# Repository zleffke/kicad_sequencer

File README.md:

# kicad_sequencer
Transverter sequencer circuit.  Based on W6PQL Design.

### Credit where its due:
[Relay Sequencer](https://www.w6pql.com/relay_sequencer.htm) from W6PQL.

#### Versions:

w6pql_sequencer - this design is nearly identical to W6PQL's at the link above. Just a kicad implementation and variations on the layout for my own projects.

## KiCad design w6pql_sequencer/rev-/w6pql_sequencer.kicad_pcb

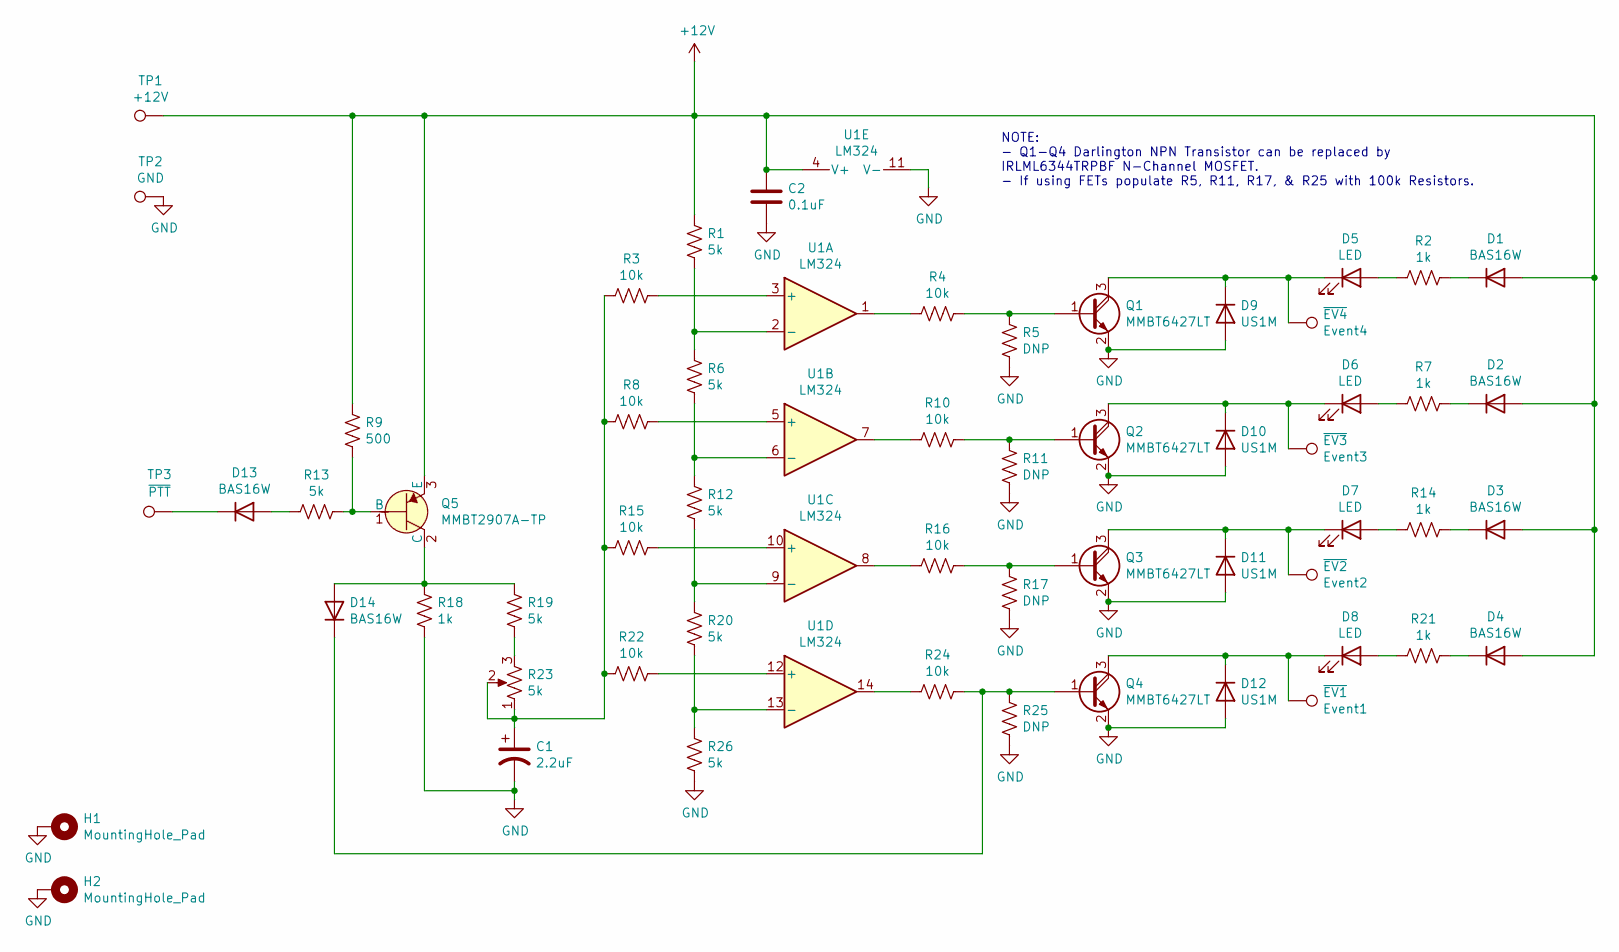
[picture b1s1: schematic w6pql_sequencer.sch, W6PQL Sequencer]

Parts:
C1: 2.2uF; CP_EIA-3216-18_Kemet-A
C2: 0.1uF; 0805
D1, D2, D3, D4, D13, D14: BAS16W; SOT-23-3
D5, D6, D7, D8: LED; LED_0805_2012Metric
D9, D10, D11, D12: US1M; D_SMA
H1, H2: MountingHole_Pad; MountingHole_3.2mm_M3_Pad_Via
Q1, Q2, Q3, Q4: MMBT6427LT; SOT-23-3
Q5: MMBT2907A-TP; SOT-23-3; MPN MMBT2907A-TP; Digi-Key_PN MMBT2907A-TPMSCT-ND
R1, R6, R12, R13, R19, R20, R26: 5k; 0805
R2, R7, R14, R18, R21: 1k; 0805
R3, R4, R8, R10, R15, R16, R22, R24: 10k; 0805
R5, R11, R17, R25: DNP; 0805
R9: 500; 0805
R23: 5k; Potentiometer_Bourns_3314G_Vertical
TP1: +12V; TestPoint_Pad_3.0x3.0mm
TP2: GND; TestPoint_Pad_3.0x3.0mm
TP3: ~PTT; TestPoint_Pad_3.0x3.0mm
U1: LM324; SOIC-14_W3.9mm
~EV1: Event1; TestPoint_Pad_4.0x4.0mm
~EV2: Event2; TestPoint_Pad_4.0x4.0mm
~EV3: Event3; TestPoint_Pad_4.0x4.0mm
~EV4: Event4; TestPoint_Pad_4.0x4.0mm

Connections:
+12V: C2.1, D1.1 (A), D2.1 (A), D3.1 (A), D4.1 (A), Q5.3 (E), R1.1, R9.1, TP1.1, U1.4 (V+)
GND: C1.2, C2.2, D9.2 (A), D10.2 (A), D11.2 (A), D12.2 (A), H1.1, H2.1, Q1.2 (E), Q2.2 (E), Q3.2 (E), Q4.2 (E), R5.1, R11.1, R17.1, R18.2, R25.1, R26.2, TP2.1, U1.11 (V-)
unnamed: C1.1, R3.2, R8.2, R15.2, R22.2, R23.1, R23.2
unnamed: D1.3 (K), R2.1
unnamed: D2.3 (K), R7.1
unnamed: D3.3 (K), R14.1
unnamed: D4.3 (K), R21.1
unnamed: D5.1 (K), D9.1 (K), Q1.3 (C), ~EV4.1
unnamed: D5.2 (A), R2.2
unnamed: D6.2 (A), R7.2
unnamed: D7.2 (A), R14.2
unnamed: D8.2 (A), R21.2
unnamed: D6.1 (K), D10.1 (K), Q2.3 (C), ~EV3.1
unnamed: D7.1 (K), D11.1 (K), Q3.3 (C), ~EV2.1
unnamed: D8.1 (K), D12.1 (K), Q4.3 (C), ~EV1.1
unnamed: D13.1 (A), R13.2
unnamed: D13.3 (K), TP3.1
unnamed: D14.1 (A), Q5.2 (C), R18.1, R19.1
unnamed: D14.3 (K), Q4.1 (B), R24.1, R25.2
unnamed: Q1.1 (B), R4.1, R5.2
unnamed: Q2.1 (B), R10.1, R11.2
unnamed: Q3.1 (B), R16.1, R17.2
unnamed: Q5.1 (B), R9.2, R13.1
unnamed: R1.2, R6.1, U1.2 (-)
unnamed: R3.1, U1.3 (+)
unnamed: R4.2, U1.1
unnamed: R8.1, U1.5 (+)
unnamed: R10.2, U1.7
unnamed: R6.2, R12.1, U1.6 (-)
unnamed: R12.2, R20.1, U1.9 (-)
unnamed: R15.1, U1.10 (+)
unnamed: R16.2, U1.8
unnamed: R19.2, R23.3
unnamed: R20.2, R26.1, U1.13 (-)
unnamed: R22.1, U1.12 (+)
unnamed: R24.2, U1.14

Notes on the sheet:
NOTE: - Q1-Q4 Darlington NPN Transistor can be replaced by IRLML6344TRPBF N-Channel MOSFET. - If using FETs populate R5, R11, R17, & R25 with 100k Resistors.

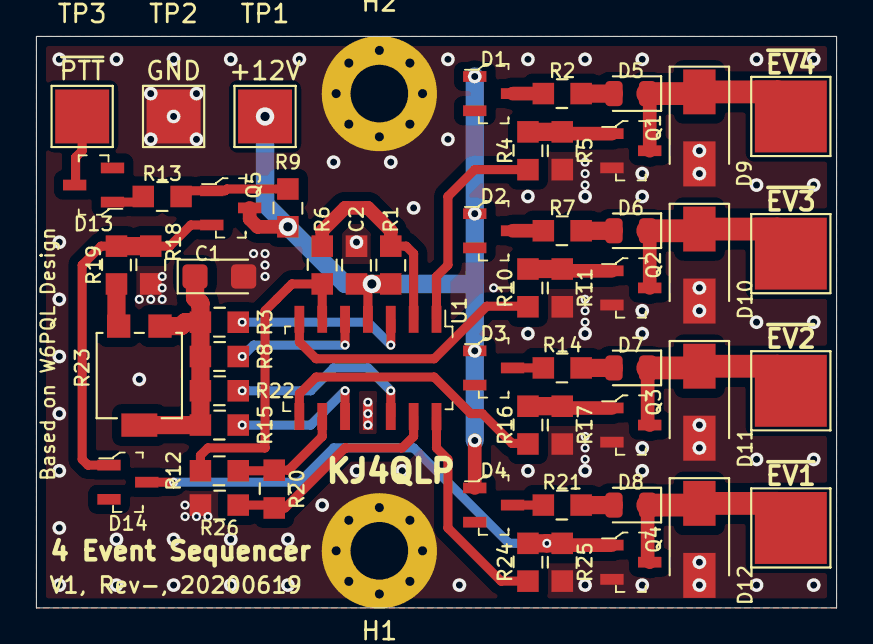
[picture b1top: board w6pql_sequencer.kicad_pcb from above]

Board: 2 copper layers, 44.4 x 31.8 mm, 53 parts (0 on the bottom side), 36 nets.

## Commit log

2020-06-19 adding v1, rev-. this commit submitted to osh park.
2020-06-27 adding schematic pdf

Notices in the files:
w6pql_sequencer/rev-/w6pql_sequencer.sch:
creativecommons.org/licenses/by/4.0
License: CC BY 4.0
